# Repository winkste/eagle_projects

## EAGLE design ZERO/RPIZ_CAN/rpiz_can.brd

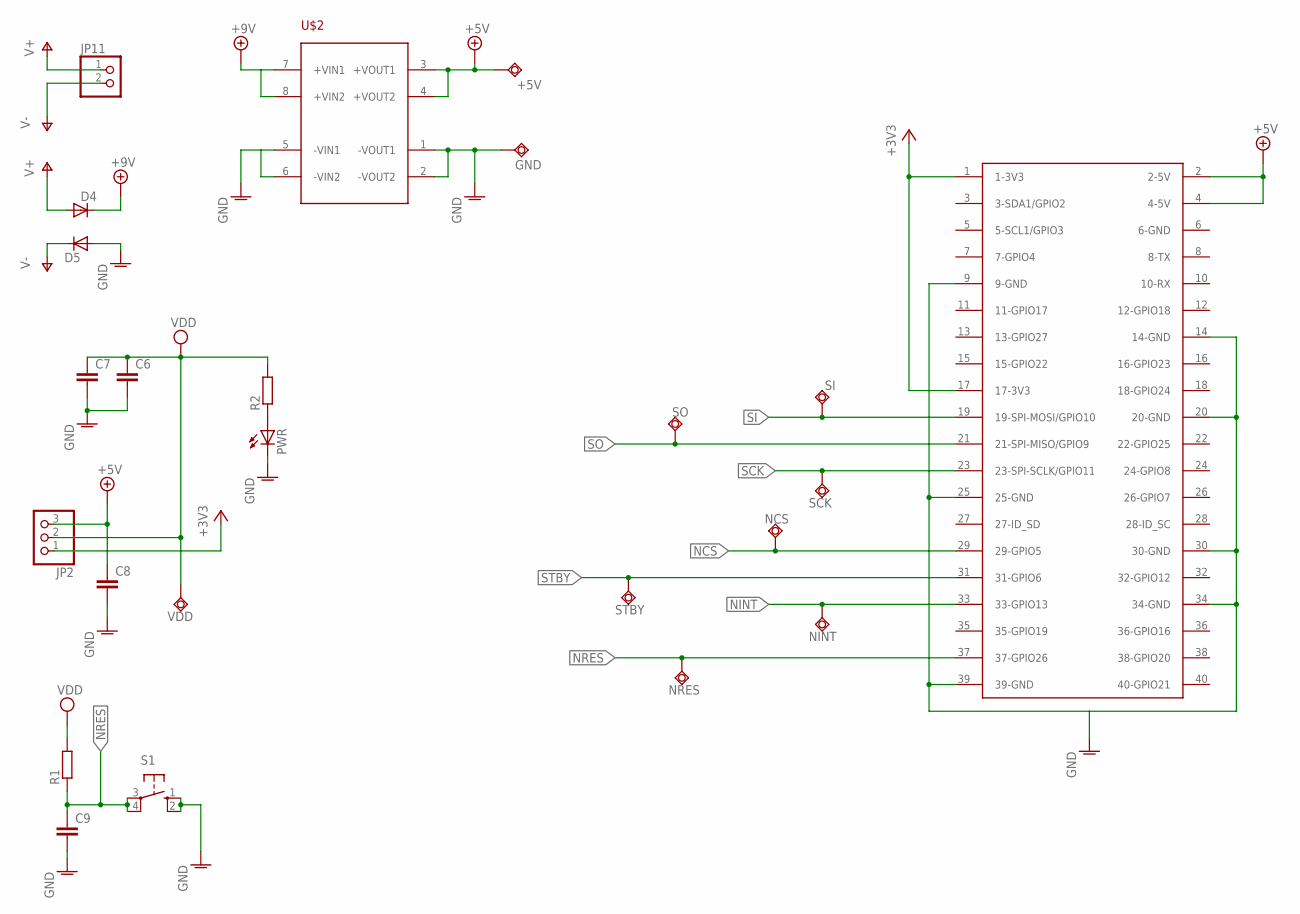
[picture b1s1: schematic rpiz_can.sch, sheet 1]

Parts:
+5V: TPSQTP20SQ; TP20SQ
C6, C7, C8, C9: C-EUC0805; C0805
D4, D5: 1N4148DO35-7; DO35-7
GND: TPSQTP20SQ; TP20SQ
JP2: PINHD-1X3; 1X03
JP11: PINHD-1X2; 1X02
NCS: TPSQTP20SQ; TP20SQ
NINT: TPSQTP20SQ; TP20SQ
NRES: TPSQTP20SQ; TP20SQ
PWR: LEDCHIP-LED0603; CHIP-LED0603
R1, R2: R-EU_R0805; R0805
S1: 10-XX; B3F-10XX
SCK: TPSQTP20SQ; TP20SQ
SI: TPSQTP20SQ; TP20SQ
SO: TPSQTP20SQ; TP20SQ
STBY: TPSQTP20SQ; TP20SQ
U$2: LVPS
U$3: RASPBERRY-PI+RASPBERRY-PI-ZERO_LONG; RASPBERRY-PI-ZERO
VDD: TPSQTP20SQ; TP20SQ

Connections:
+3V3: JP2.1, U$3.1 (1-3V3), U$3.17 (17-3V3)
+5V: +5V.TP, C8.1, JP2.3, U$2.3 (+VOUT1), U$2.4 (+VOUT2), U$3.2 (2-5V), U$3.4 (4-5V)
+9V: D4.C, U$2.7 (+VIN1), U$2.8 (+VIN2)
AGND: C6.2, C7.2
GND: C8.2, C9.2, D5.A, GND.TP, PWR.C, S1.1 (S), S1.2 (S1), U$2.1 (-VOUT1), U$2.2 (-VOUT2), U$2.5 (-VIN1), U$2.6 (-VIN2), U$3.9 (9-GND), U$3.14 (14-GND), U$3.20 (20-GND), U$3.25 (25-GND), U$3.30 (30-GND), U$3.34 (34-GND), U$3.39 (39-GND); also elsewhere on the board
unnamed: PWR.A, R2.1
NCS: NCS.TP, U$3.29 (29-GPIO5); also elsewhere on the board
NINT: NINT.TP, U$3.33 (33-GPIO13); also elsewhere on the board
NRES: C9.1, NRES.TP, R1.1, S1.3, S1.4 (P1), U$3.37 (37-GPIO26); also elsewhere on the board
SCK: SCK.TP, U$3.23 (23-SPI-SCLK/GPIO11); also elsewhere on the board
SI: SI.TP, U$3.19 (19-SPI-MOSI/GPIO10); also elsewhere on the board
SO: SO.TP, U$3.21 (21-SPI-MISO/GPIO9); also elsewhere on the board
STBY: STBY.TP, U$3.31 (31-GPIO6); also elsewhere on the board
V+: D4.A, JP11.1
V-: D5.C, JP11.2
VDD: C6.1, C7.1, JP2.2, R1.2, R2.2, VDD.TP; also elsewhere on the board

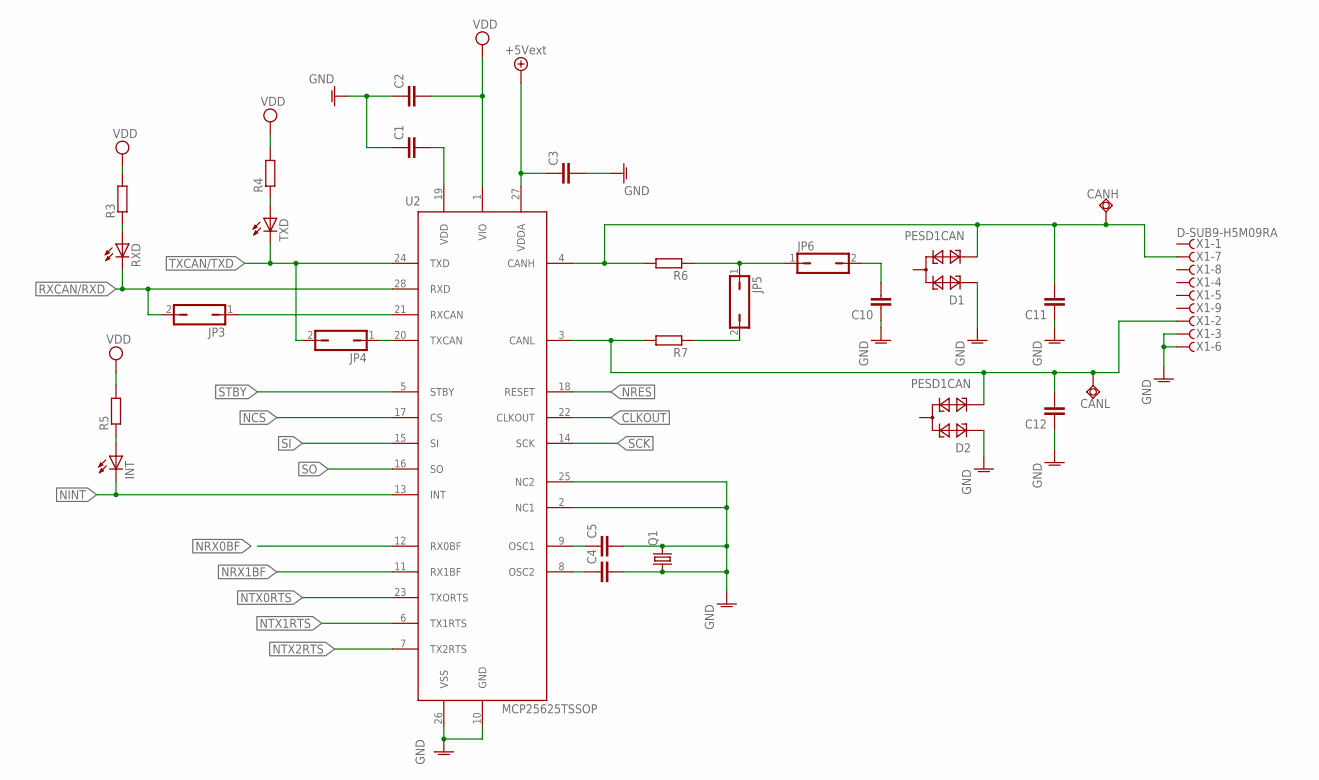
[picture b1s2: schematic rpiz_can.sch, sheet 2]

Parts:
C1, C2, C3, C4, C5, C10, C11, C12: C-EUC0805; C0805
CANH: TPSQTP20SQ; TP20SQ
CANL: TPSQTP20SQ; TP20SQ
D1, D2: PESD1CAN; SOT23
INT: LEDCHIP-LED0603; CHIP-LED0603
JP3, JP4, JP5, JP6: JP1Q; JP1
Q1: CRYSTALSM49; SM49
R3, R4, R5, R6, R7: R-EU_R0805; R0805
RXD: LEDCHIP-LED0603; CHIP-LED0603
TXD: LEDCHIP-LED0603; CHIP-LED0603
U2: MCP25625TSSOP; TSSOP-28
X1: D-SUB9-H5M09RA; H5M09RA

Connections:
+5V/1: C3.1, U2.27 (VDDA)
CLKOUT: U2.22 (CLKOUT)
GND: C1.1, C2.1, C3.2, C4.2, C5.2, C10.1, C11.1, C12.1, D1.1, D2.1, Q1.1, Q1.2, U2.2 (NC1), U2.10 (GND), U2.25 (NC2), U2.26 (VSS), X1.3, X1.6; also elsewhere on the board
unnamed: JP3.1, U2.21 (RXCAN)
unnamed: R3.1, RXD.A
unnamed: JP4.1, U2.20 (TXCAN)
unnamed: R4.1, TXD.A
unnamed: INT.A, R5.1
unnamed: C5.1, U2.9 (OSC1)
unnamed: C4.1, U2.8 (OSC2)
unnamed: C11.2, CANH.TP, D1.2, R6.2, U2.4 (CANH), X1.7
unnamed: C1.2, U2.19 (VDD)
unnamed: C12.2, CANL.TP, D2.2, R7.2, U2.3 (CANL), X1.2
unnamed: JP5.1, JP6.1, R6.1
unnamed: JP5.2, R7.1
unnamed: C10.2, JP6.2
NCS: U2.17 (CS); also elsewhere on the board
NINT: INT.C, U2.13 (INT); also elsewhere on the board
NRES: U2.18 (RESET); also elsewhere on the board
NRX0BF: U2.12 (RX0BF)
NRX1BF: U2.11 (RX1BF)
NTX0RTS: U2.23 (TXORTS)
NTX1RTS: U2.6 (TX1RTS)
NTX2RTS: U2.7 (TX2RTS)
RXCAN/RXD: JP3.2, RXD.C, U2.28 (RXD)
SCK: U2.14 (SCK); also elsewhere on the board
SI: U2.15 (SI); also elsewhere on the board
SO: U2.16 (SO); also elsewhere on the board
STBY: U2.5 (STBY); also elsewhere on the board
TXCAN/TXD: JP4.2, TXD.C, U2.24 (TXD)
VDD: C2.2, R3.2, R4.2, R5.2, U2.1 (VIO); also elsewhere on the board

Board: 2 copper layers, 51 parts (16 on the bottom side), 32 nets, no tracks yet.

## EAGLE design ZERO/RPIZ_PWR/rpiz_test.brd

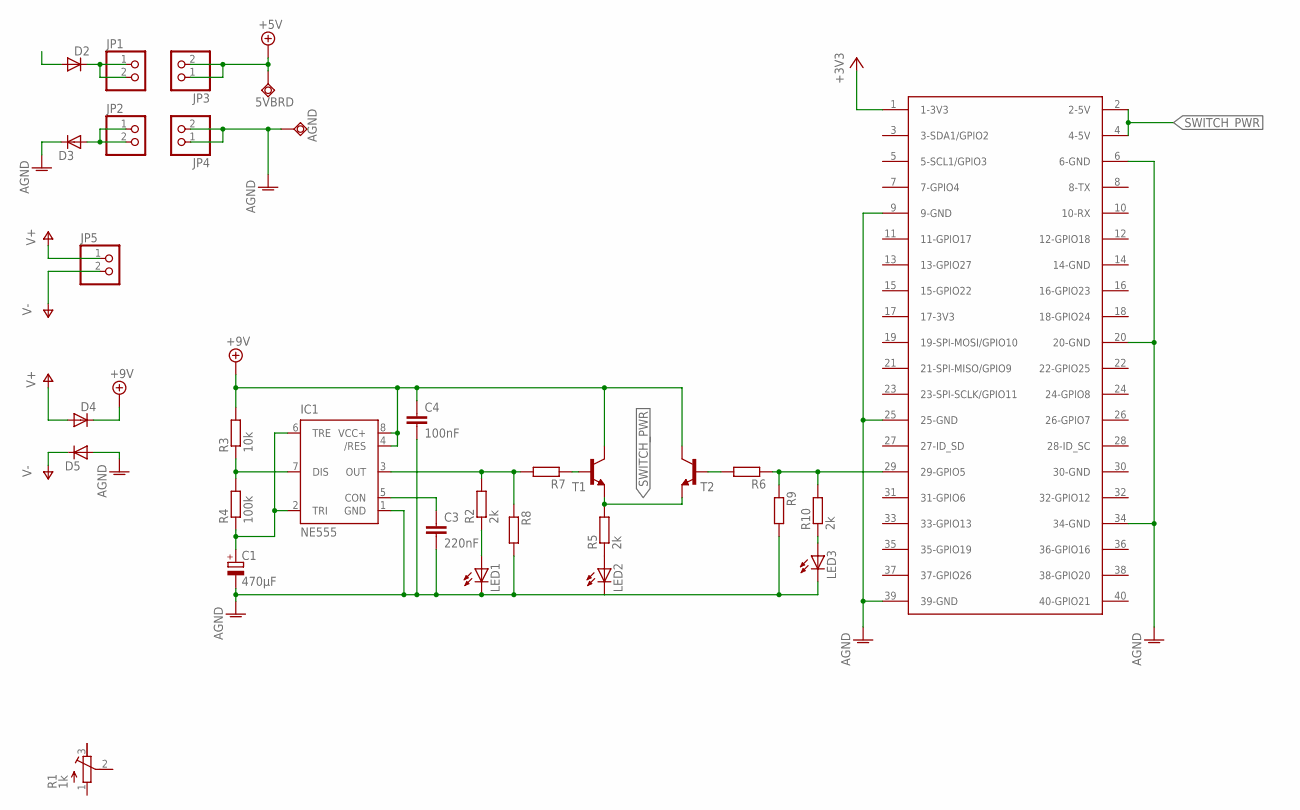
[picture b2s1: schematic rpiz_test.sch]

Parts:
5VBRD: TPSQTP20SQ; TP20SQ
AGND: TPSQTP20SQ; TP20SQ
C1: 470µF; E5-10,5
C3: 220nF; C050-030X075
C4: 100nF; C050-030X075
D2, D3, D4, D5: 1N4148DO35-7; DO35-7
IC1: NE555; DIL-08
JP1, JP2, JP3, JP4, JP5: PINHD-1X2; 1X02
LED1, LED2, LED3: LED5MM
R1: 1k; RTRIM64W
R2, R5, R10: 2k; 0207/10
R3: 10k; 0207/10
R4: 100k; 0207/10
R6, R7, R8, R9: R-EU_R0805; R0805
T1, T2: BC547-NPN-TO92-CBE; TO92-CBE
U$1: RASPBERRY-PI+PIZERO; RASPBERRY-PI-ZERO

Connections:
+3V3: U$1.1 (1-3V3)
+5V: 5VBRD.TP, JP3.1, JP3.2
+9V: C4.1, D4.C, IC1.4 (/RES), IC1.8 (VCC+), R3.2, T1.C, T2.C
AGND: AGND.TP, C1.-, C3.2, C4.2, D3.C, D5.A, IC1.1 (GND), JP4.1, JP4.2, LED1.K (C), LED2.K (C), LED3.K (C), R8.2, R9.2, U$1.6 (6-GND), U$1.9 (9-GND), U$1.20 (20-GND), U$1.25 (25-GND), U$1.34 (34-GND), U$1.39 (39-GND)
GPA0: IC1.3 (OUT), R2.2, R7.2, R8.1
unnamed: D2.C, JP1.1, JP1.2
unnamed: D3.A, JP2.1, JP2.2
unnamed: IC1.7 (DIS), R3.1, R4.2
unnamed: C1.+, IC1.2 (TRI), IC1.6 (TRE), R4.1
unnamed: LED2.A, R5.1
unnamed: C3.1, IC1.5 (CON)
unnamed: R7.1, T1.B
unnamed: LED1.A, R2.1
unnamed: R6.2, T2.B
unnamed: R6.1, R9.1, R10.2, U$1.29 (29-GPIO5)
unnamed: LED3.A, R10.1
SWITCH_PWR: R5.2, T1.E, T2.E, U$1.2 (2-5V), U$1.4 (4-5V)
V+: D4.A, JP5.1
V-: D5.C, JP5.2

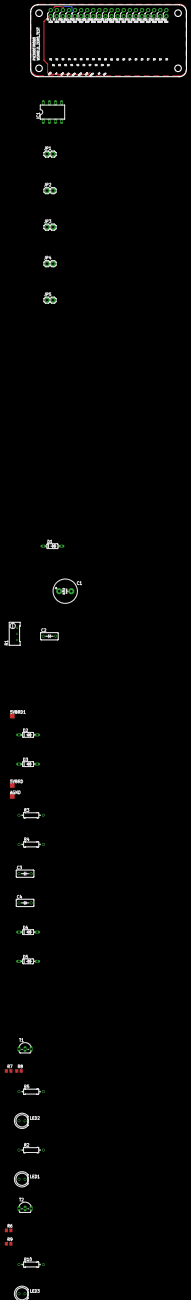
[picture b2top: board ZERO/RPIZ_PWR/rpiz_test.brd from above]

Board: 2 copper layers, 65.0 x 30.0 mm, 34 parts (0 on the bottom side), 18 nets.

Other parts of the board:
5VBRD1: TPSQTP20SQ; TP20SQ
C2: 220nF; C050-030X075
D1: 1N4148DO35-7; DO35-7

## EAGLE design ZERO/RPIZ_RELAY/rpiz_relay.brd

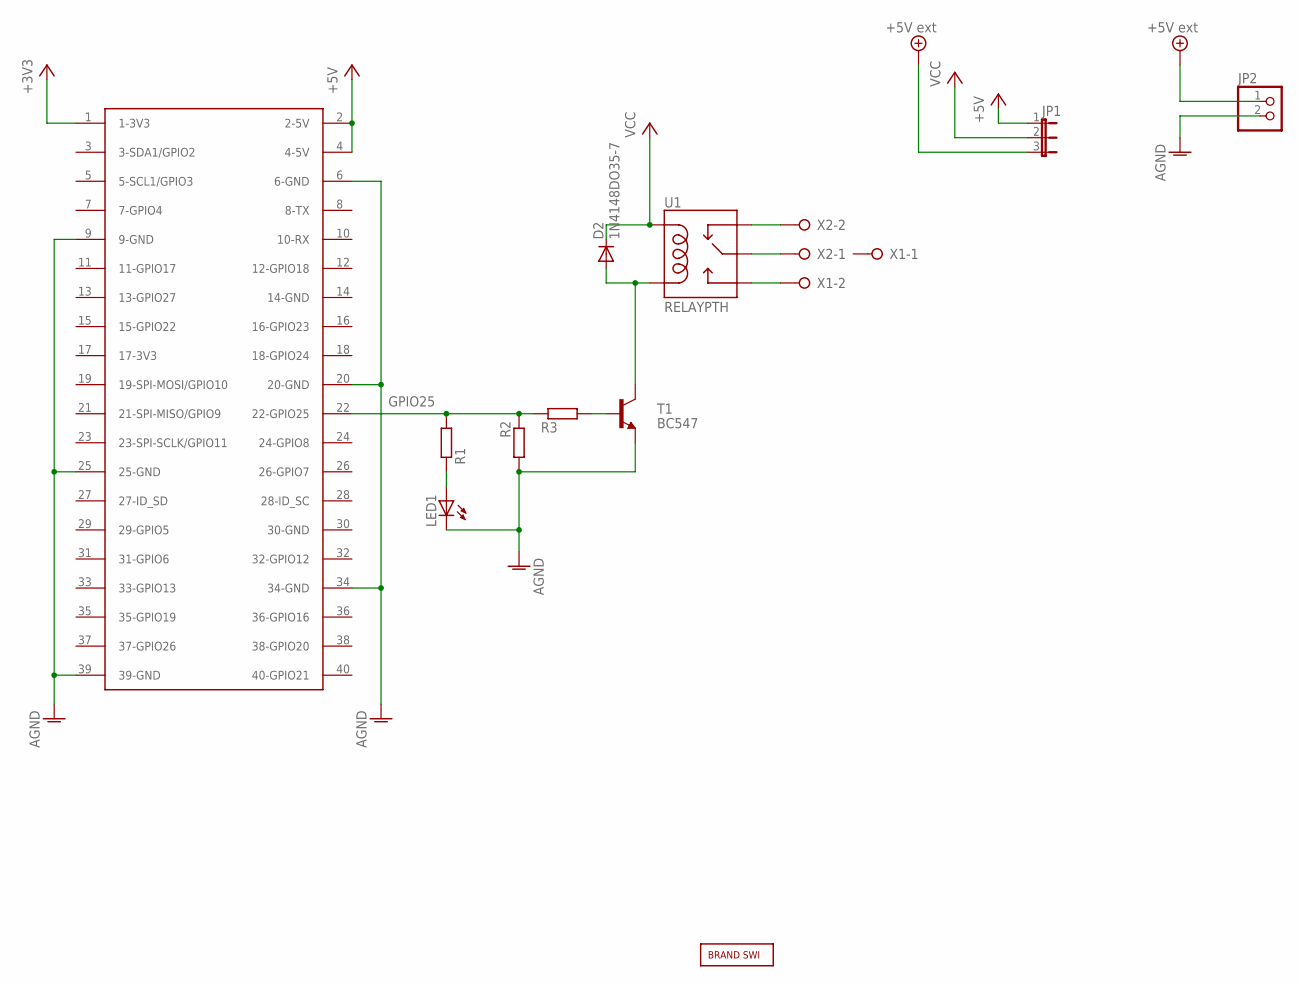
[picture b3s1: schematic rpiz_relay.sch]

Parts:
D2: 1N4148DO35-7; DO35-7
JP1: JP2E; JP2
JP2: PINHD-1X2; 1X02
LED1: LEDCHIP-LED0805; CHIP-LED0805
R1, R2, R3: R-EU_R0805; R0805
T1: BC547; TO92
U1: RELAYPTH; SRD-05VDC-SL-C
U$1: RASPBERRY-PI+PIZERO; RASPBERRY-PI-ZERO
U$2: BRAND_SWI5X7; BRAND_SWI_5X7
X1, X2: W237-02P; W237-132

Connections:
+3V3: U$1.1 (1-3V3)
+5V: JP1.1, U$1.2 (2-5V), U$1.4 (4-5V)
+5V/1: JP1.3, JP2.1
AGND: JP2.2, LED1.C, R2.2, T1.1 (E), U$1.6 (6-GND), U$1.9 (9-GND), U$1.20 (20-GND), U$1.25 (25-GND), U$1.34 (34-GND), U$1.39 (39-GND)
GPIO25: R1.2, R2.1, R3.1, U$1.22 (22-GPIO25)
unnamed: U1.SWCLOSED (SWCLOSE), X2.2
unnamed: U1.SWCOMMON, X2.1
unnamed: U1.SWOPEN, X1.2
unnamed: D2.A, T1.3 (C), U1.COIL0
unnamed: R3.2, T1.2 (B)
unnamed: LED1.A, R1.1
VCC: D2.C, JP1.2, U1.COIL1

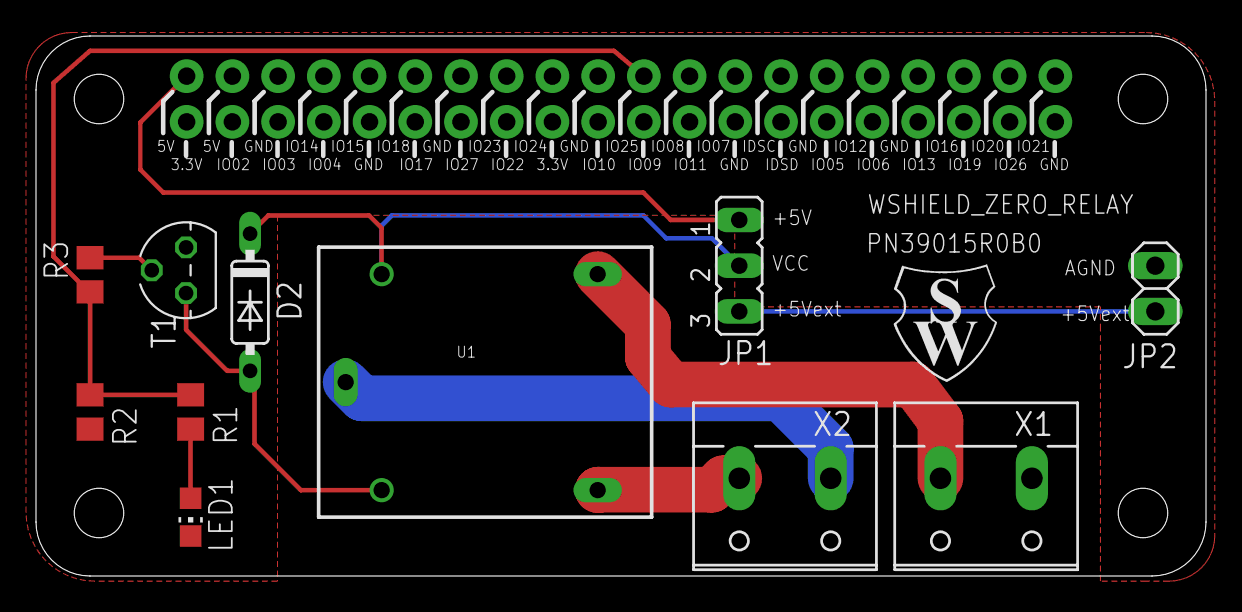
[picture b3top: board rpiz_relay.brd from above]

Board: 2 copper layers, 65.0 x 30.0 mm, 13 parts (0 on the bottom side), 11 nets.

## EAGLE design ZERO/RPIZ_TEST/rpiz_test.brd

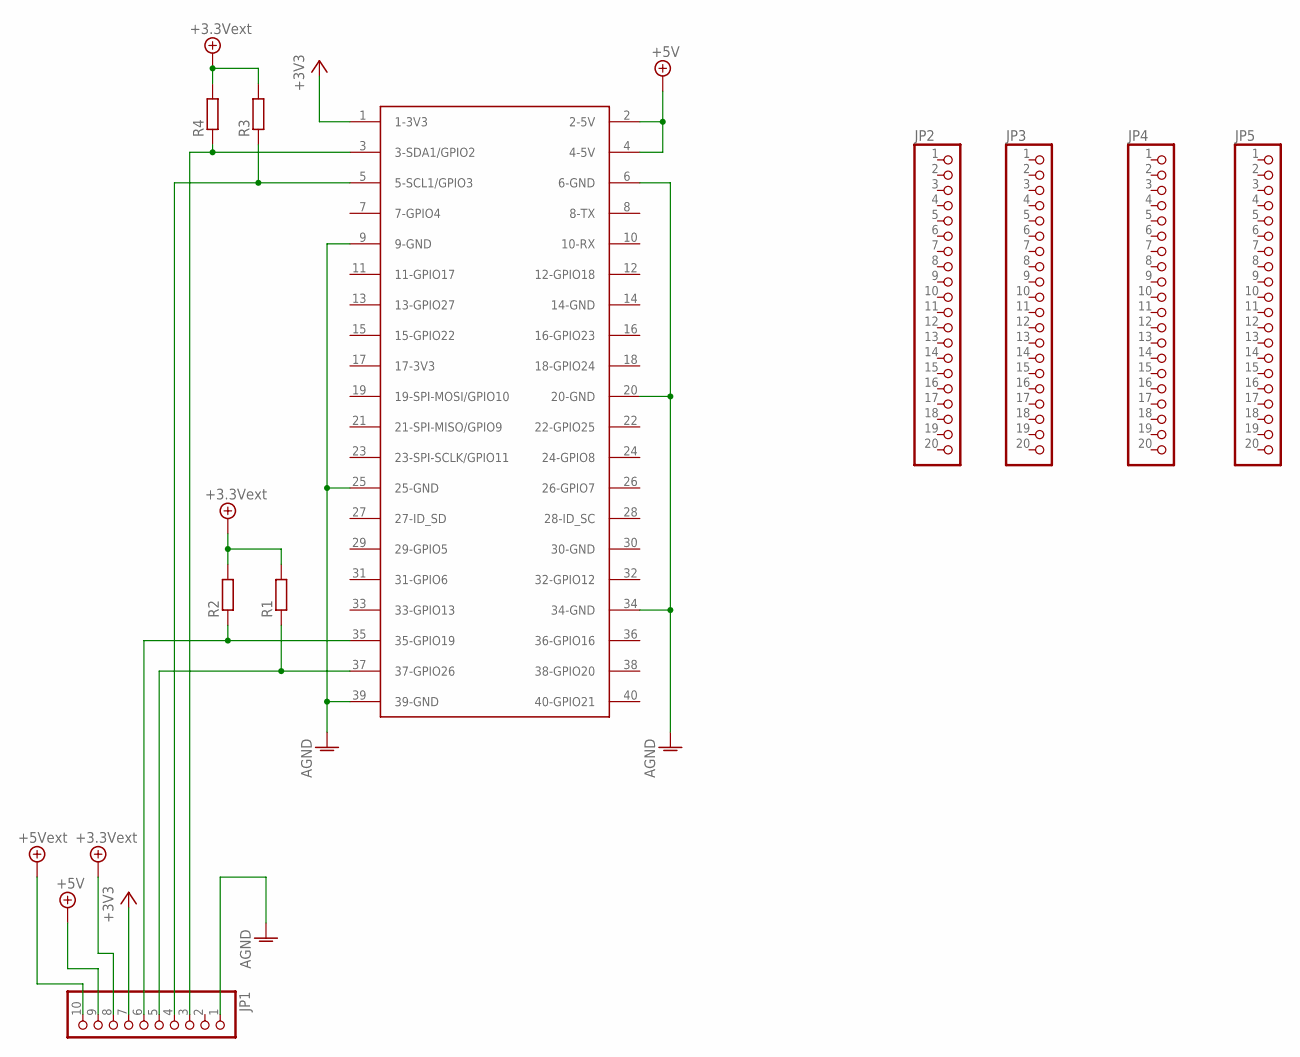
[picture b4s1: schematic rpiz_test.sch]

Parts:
JP1: PINHD-1X10; 1X10
JP2, JP3, JP4, JP5: PINHD-1X20; 1X20
R1, R2, R3, R4: R-EU_R0805; R0805
U$1: RASPBERRY-PI+PIZERO; RASPBERRY-PI-ZERO

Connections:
3.3VEXT: JP1.8, R1.2, R2.2, R3.2, R4.2
+3V3: JP1.7, U$1.1 (1-3V3)
+5V: JP1.9, U$1.2 (2-5V), U$1.4 (4-5V)
+5V/1: JP1.10
AGND: JP1.1, U$1.6 (6-GND), U$1.9 (9-GND), U$1.20 (20-GND), U$1.25 (25-GND), U$1.34 (34-GND), U$1.39 (39-GND)
unnamed: JP1.3, R4.1, U$1.3 (3-SDA1/GPIO2)
unnamed: JP1.4, R3.1, U$1.5 (5-SCL1/GPIO3)
unnamed: JP1.5, R1.1, U$1.37 (37-GPIO26)
unnamed: JP1.6, R2.1, U$1.35 (35-GPIO19)

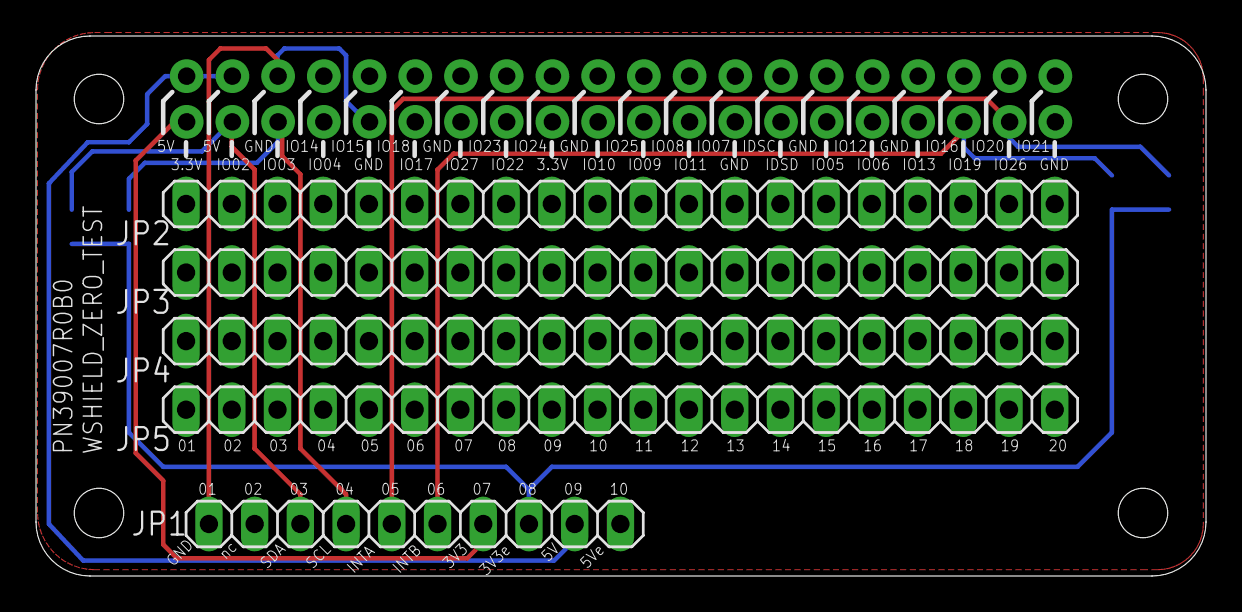
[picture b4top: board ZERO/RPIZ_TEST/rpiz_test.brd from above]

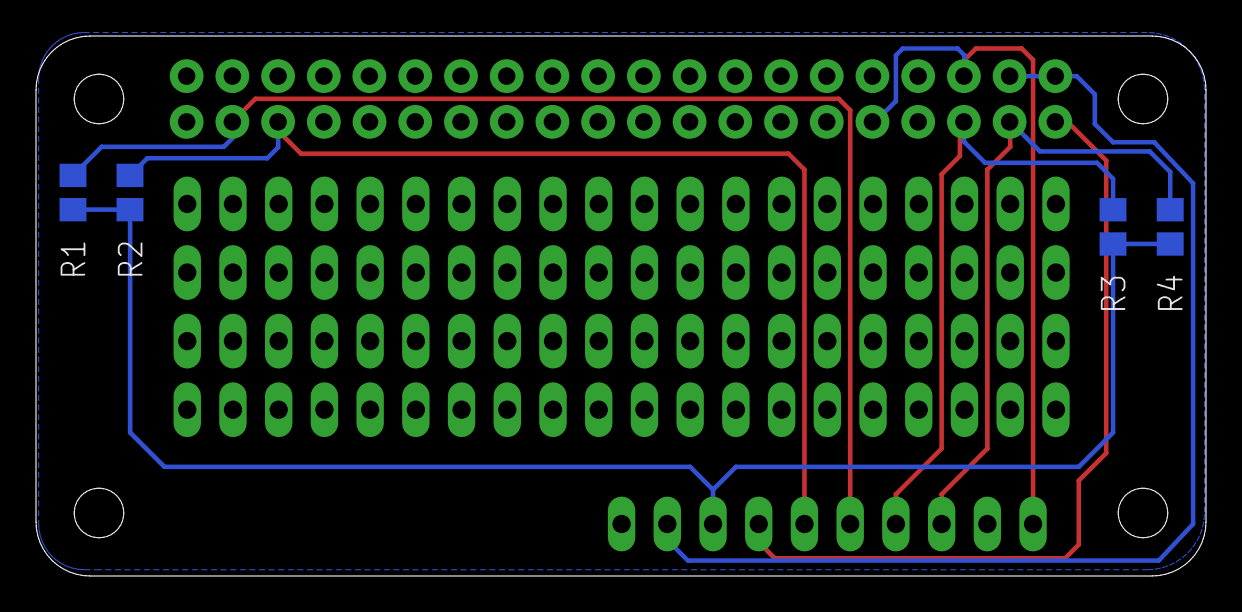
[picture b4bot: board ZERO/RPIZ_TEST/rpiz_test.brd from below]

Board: 2 copper layers, 65.0 x 30.0 mm, 10 parts (4 on the bottom side), 8 nets.
